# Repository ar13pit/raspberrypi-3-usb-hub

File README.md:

# USB Hub for SMPS powered Raspberry Pi 3 Cluster
The repository contains Schematic and PCB files for SMPS powered USB Power Hub for a Raspberry Pi Cluster.

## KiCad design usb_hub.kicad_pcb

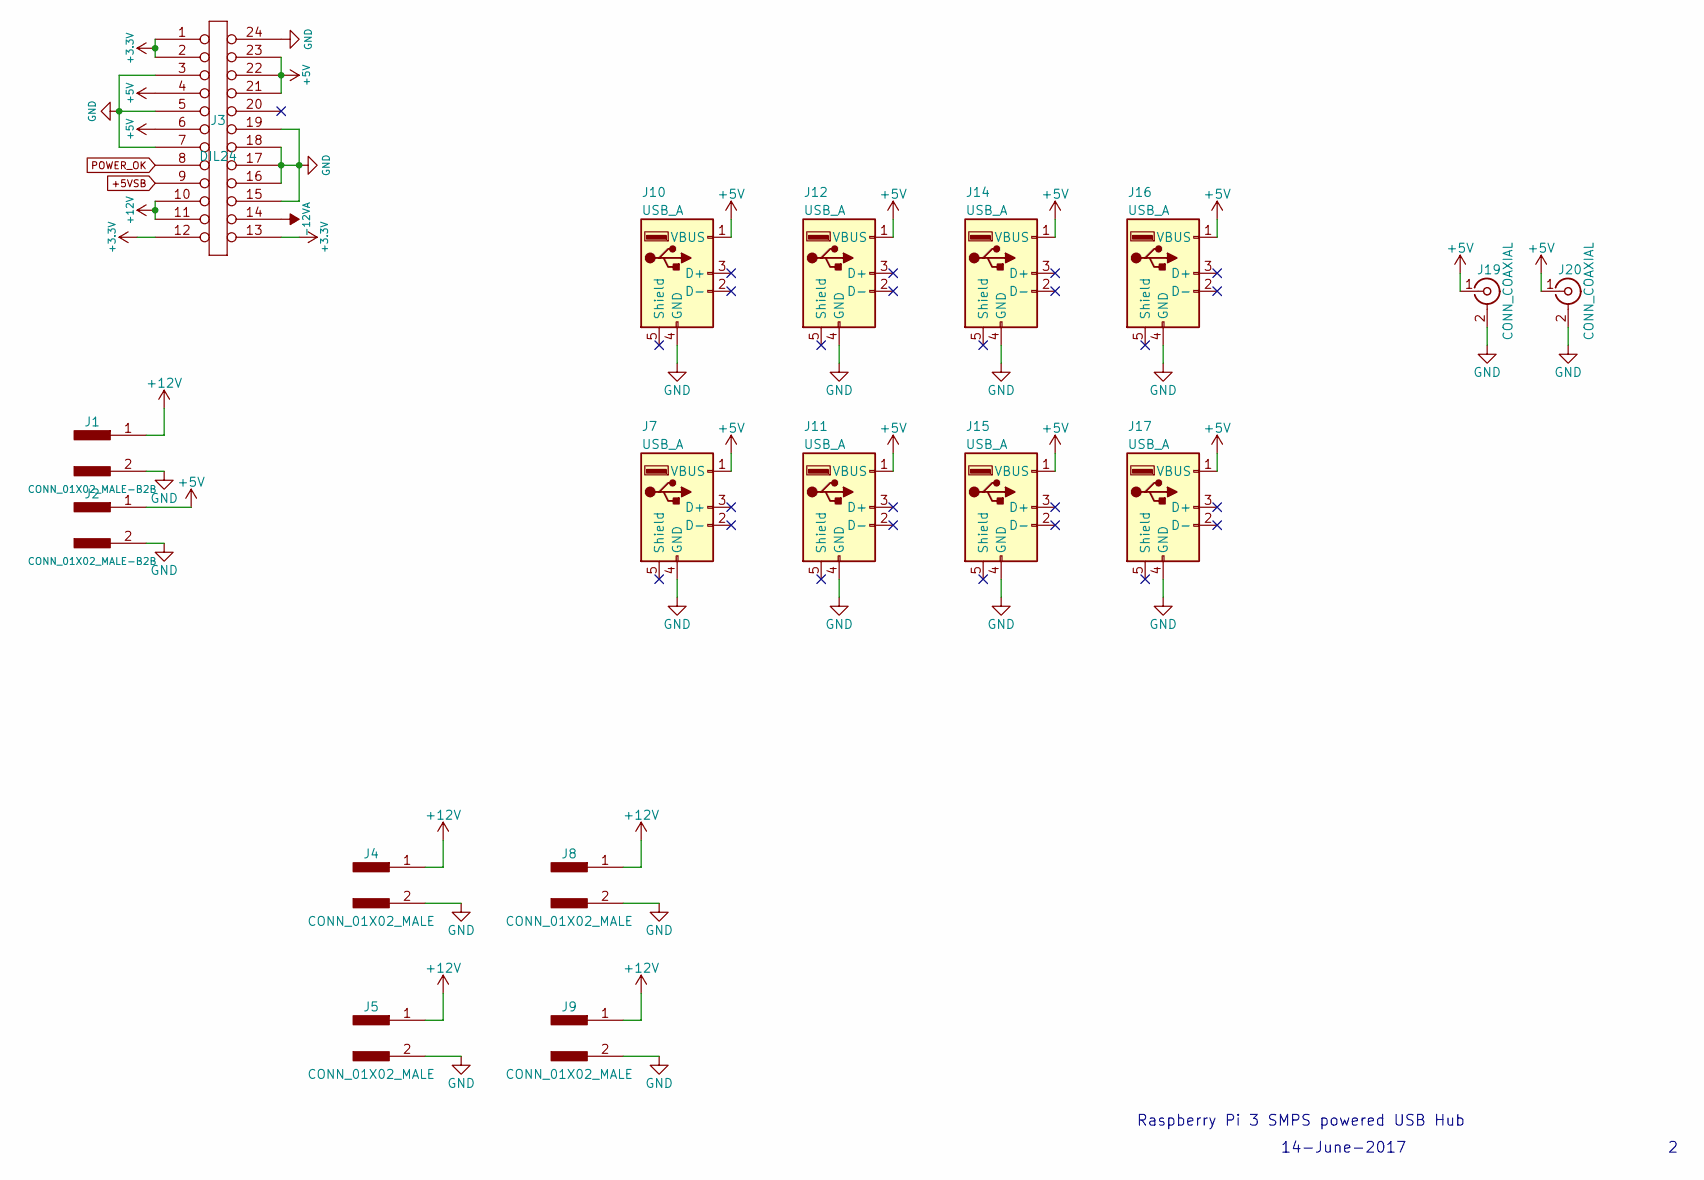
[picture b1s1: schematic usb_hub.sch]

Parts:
J1, J2: CONN_01X02_MALE-B2B; Molex_MiniFit-JR-5556-02A_2x01x4.20mm_Straight
J3: DIL24; ATX_Wire_On_Board
J4, J5, J8, J9: CONN_01X02_MALE; JST_XH_B02B-XH-A_02x2.50mm_Straight
J7, J10, J11, J12, J14, J15, J16, J17: USB_A
J19, J20: CONN_COAXIAL; BARREL_JACK

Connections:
+3V3: J3.1, J3.2, J3.12, J3.13
+5V: J2.1, J3.4, J3.6, J3.21, J3.22, J3.23, J7.1 (VBUS), J10.1 (VBUS), J11.1 (VBUS), J12.1 (VBUS), J14.1 (VBUS), J15.1 (VBUS), J16.1 (VBUS), J17.1 (VBUS), J19.1 (In), J20.1 (In)
+5VSB: J3.9
+12V: J1.1, J3.10, J3.11, J4.1, J5.1, J8.1, J9.1
-12VA: J3.14
GND: J1.2, J2.2, J3.3, J3.5, J3.7, J3.15, J3.16, J3.17, J3.18, J3.19, J3.24, J4.2, J5.2, J7.4 (GND), J8.2, J9.2, J10.4 (GND), J11.4 (GND), J12.4 (GND), J14.4 (GND), J15.4 (GND), J16.4 (GND), J17.4 (GND), J19.2 (Ext), J20.2 (Ext)
POWER_OK: J3.8

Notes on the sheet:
Raspberry Pi 3 SMPS powered USB Hub
14-June-2017

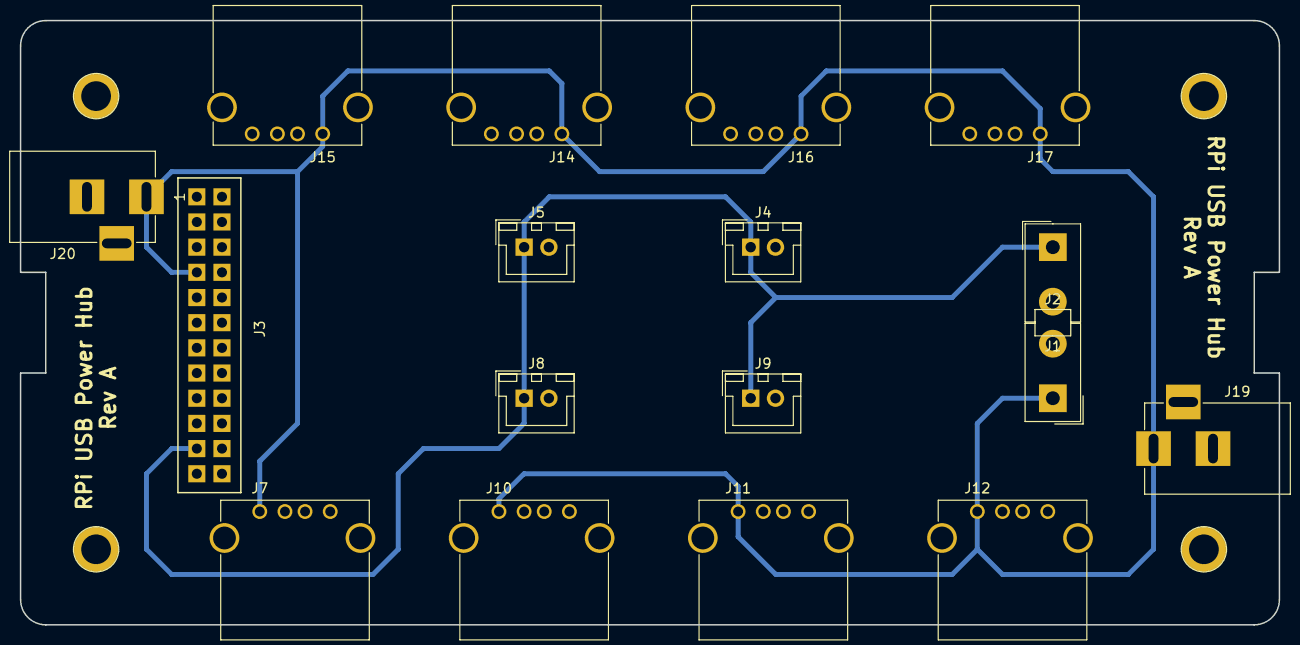
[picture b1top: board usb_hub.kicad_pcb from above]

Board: 2 copper layers, 127.0 x 61.0 mm, 17 parts (0 on the bottom side), 4 nets.

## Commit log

2017-06-14 basic schematic ready
2017-06-15 corrected pcb outline
2017-06-16 Rev A complete
